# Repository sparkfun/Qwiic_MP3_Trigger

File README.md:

SparkFun Qwiic MP3 Trigger
========================================

[*SparkFun Qwiic MP3 Trigger (DEV-15165)*](https://www.sparkfun.com/products/15165)

This repo is the hardware repo for the Qwiic MP3 Trigger.

Sometimes you just need an MP3 to play. Whether it's a theme song as you enter the room or a pirate cackling when a dollar [gets donated](https://github.com/nseidle/Money_Vacuum) to the kid's museum. The Qwiic MP3 Trigger takes care of all the necessary bits, all you need to do is send a simple I2C command and listen.

The Qwiic MP3 Trigger comes loaded with everything a user may need. Connecting a USB C cable enumerates the Qwiic MP3 Trigger as a jump drive. Simply plug in the Qwiic MP3 Trigger and you'll be transferring MP3s. No need for drivers and no need for WAV or Vorbis conversion! Sound output is provided via a headphone jack or poke-home connector allowing an external speaker to be connected without soldering. The speaker is boosted by a Class-D mono amplifier capable of outputting up to 1.4W. What does 1.4W mean? It's incredibly loud; great for making sure your mech effects are heard on the *con floor and wonderful for annoying your officemates. Volume is software selectable between 32 levels. Equalization can be tuned to be sure your classical hits sound different from your jazz dance routines (in all seriousness EQ selection is available but it's pretty paltry).

And if you don't want to deal with *any* programming, there are four trigger pins. When pin 3 is pulled low the T003.mp3 file will immediately be played. This allows you to start playing sound effects with the touch of a button! By pulling multiple pins down simultaneously the four triggers can play up to ten tracks: T001 to T010.

All settings including volume, EQ, and I2C address are stored in NVM and loaded at each power up. The I2C address of the Qwiic MP3 Trigger can be modified via a solder jumper or be assigned using a software command. Multiple Qwiic MP3 Triggers can be chained together on a single bus allowing for simultaneous track mixing and triggering.

We've written an extensive Arduino library to make MP3 playing over I2C a breeze. Play track X, change volume, play next/previous, check if track is playing, stop play, change EQ, and change I2C address are all supported.

The I2C address of Qwiic MP3 Trigger is software configurable which means you can hookup over 100 on a single I2C bus!

This board is one of our many [Qwiic](https://www.sparkfun.com/qwiic) compatible boards! Simply plug and go. No soldering, no figuring out which is SDA or SCL, and no voltage regulation or translation required!

SparkFun labored with love to create this code. Feel like supporting open source hardware? 
Buy a [breakout board](https://www.sparkfun.com/products/15165) from SparkFun!

Repository Contents
-------------------

* **/Documents** - Datasheets
* **/Hardware** - Eagle design files (.brd, .sch)

Documentation
--------------
* **[Qwiic MP3 Trigger Hookup Guide](https://learn.sparkfun.com/tutorials/qwiic-mp3-trigger-hookup-guide)** - Hookup guide for the Qwiic MP3 Trigger
* **[Installing an Arduino Library Guide](https://learn.sparkfun.com/tutorials/installing-an-arduino-library)** - Basic information on how to install an Arduino library.
* **[Arduino Library](https://github.com/sparkfun/SparkFun_Qwiic_MP3_Trigger_Arduino_Library)** - Library if you decide to use an Arduino via serial I2C.

License Information
-------------------

This product is _**open source**_! 

If you have any questions or concerns on licensing, please contact techsupport@sparkfun.com.

Please use, reuse, and modify these files as you see fit. Please maintain attribution to SparkFun Electronics and release any derivative under the same license.

Distributed as-is; no warranty is given.

- Your friends at SparkFun.

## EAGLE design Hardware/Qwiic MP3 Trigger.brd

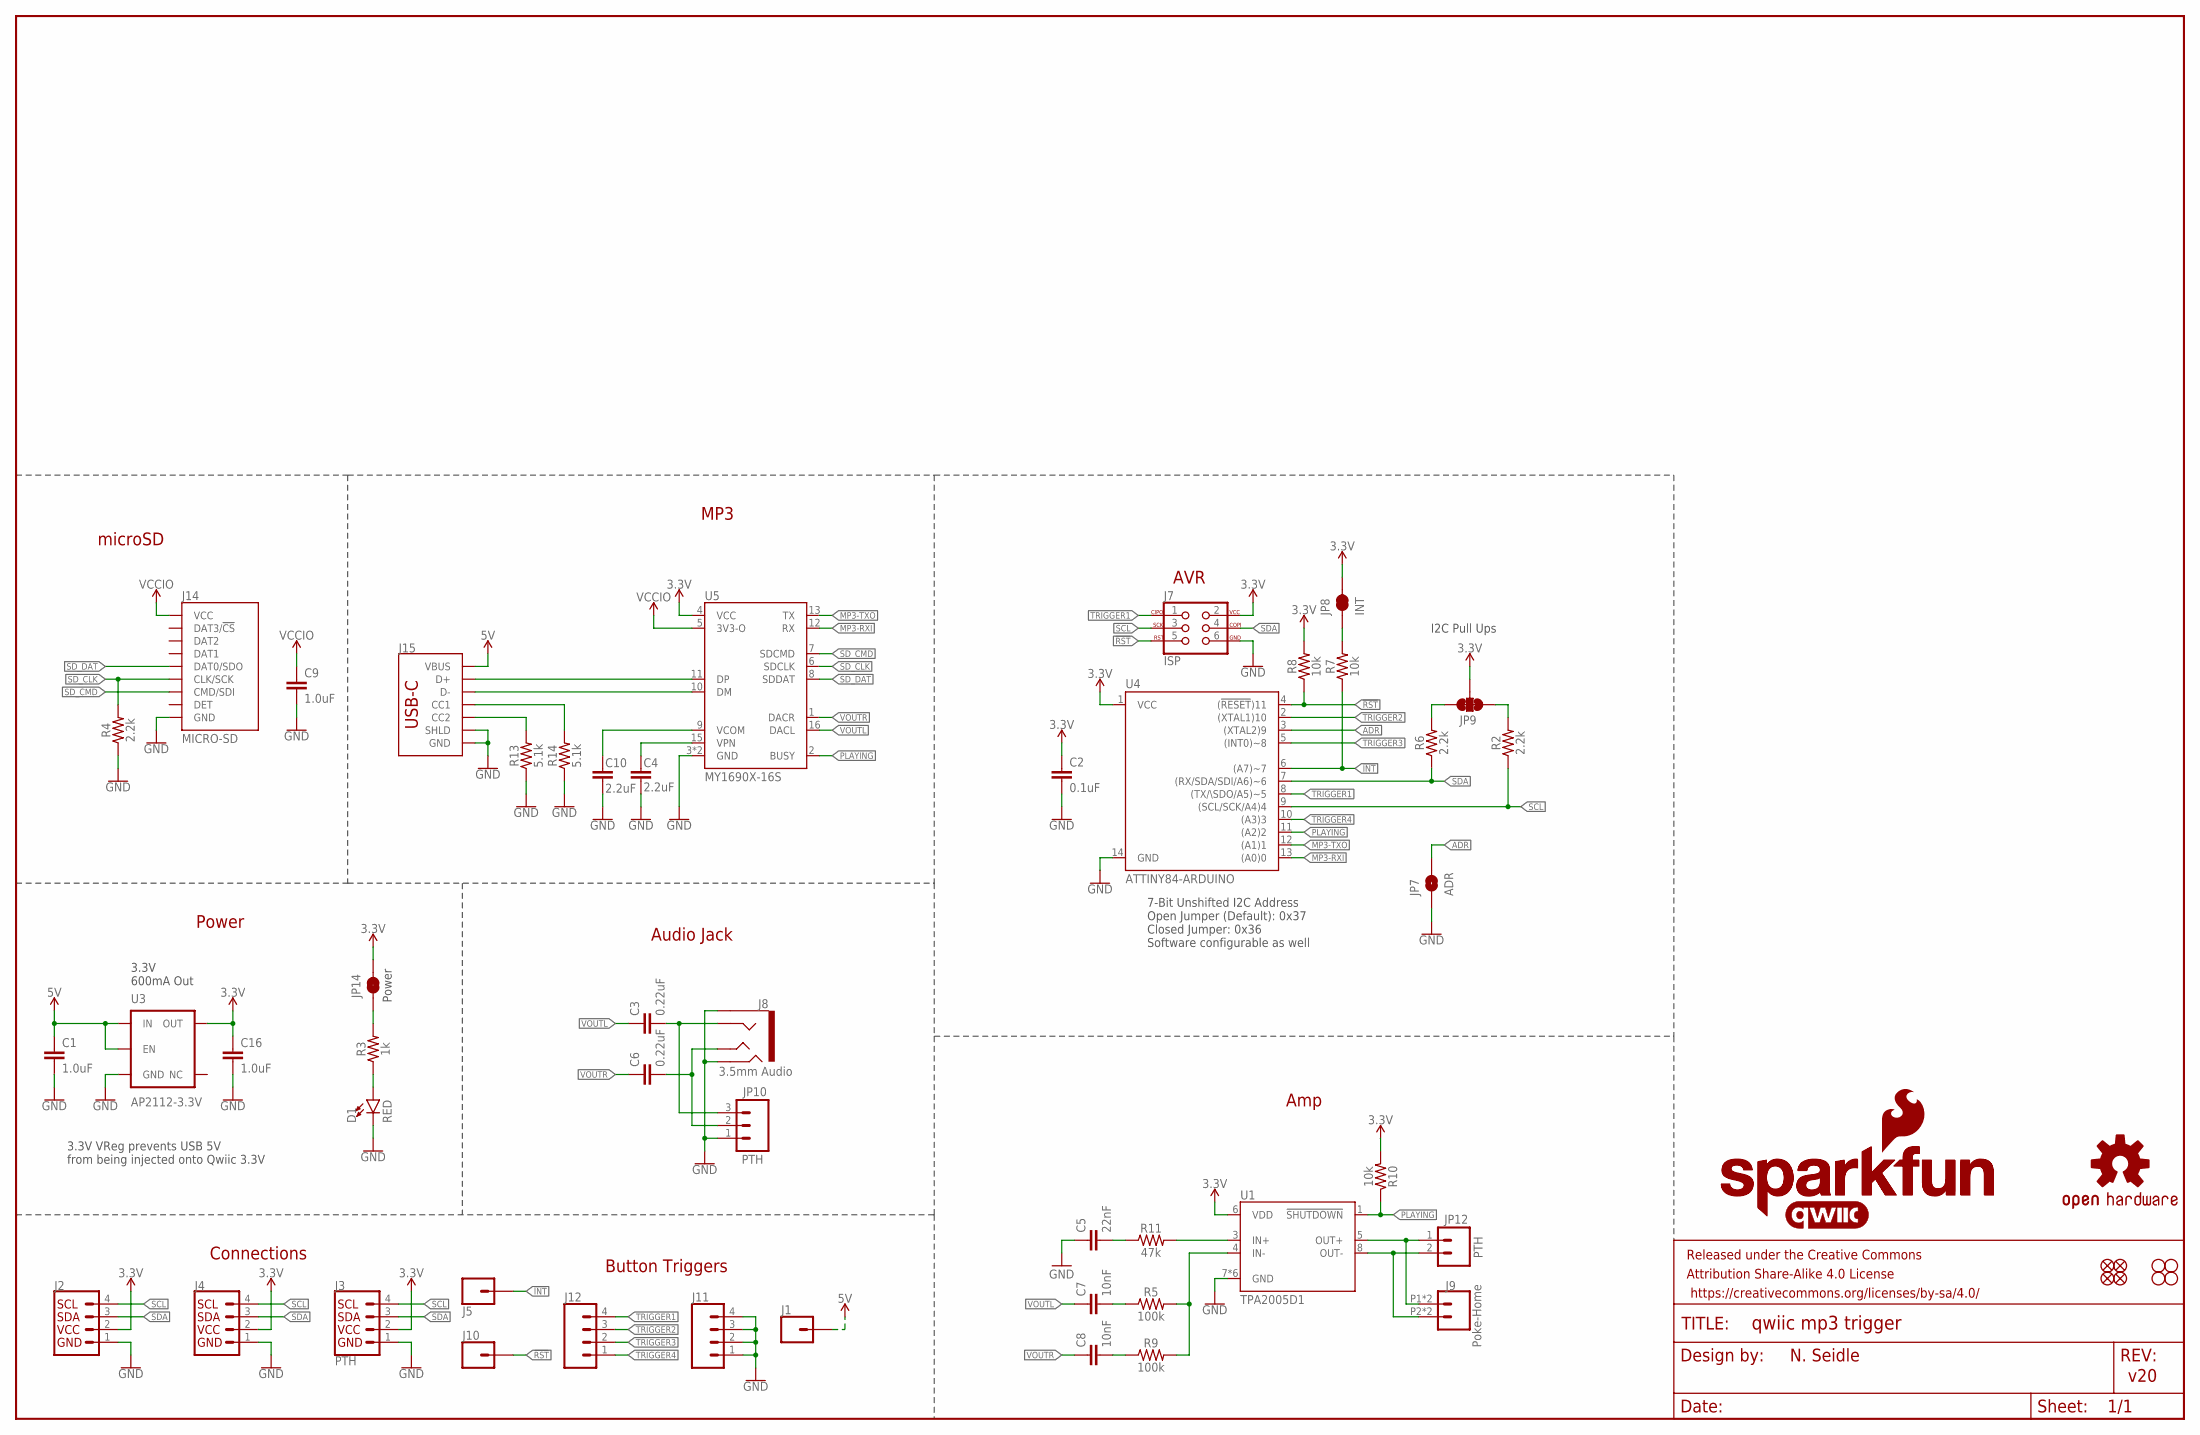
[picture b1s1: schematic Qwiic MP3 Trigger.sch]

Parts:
C1, C9, C16: 1.0uF; 0603
C2: 0.1uF; 0603
C3, C6: 0.22uF; 0603
C4, C10: 2.2uF; 0603
C5: 22nF; 0603
C7, C8: 10nF; 0603
D1: RED; LED-0603
FRAME1: FRAME-LEDGER; CREATIVE_COMMONS
J1, J5, J10: CONN_01PTH_NO_SILK_YES_STOP; 1X01_NO_SILK
J2, J4: QWIIC_RIGHT_ANGLE; JST04_1MM_RA
J3: PTH; 1X04_NO_SILK
J7: ISP; 2X3_TEST_POINTS
J8: 3.5mm Audio; AUDIO_JACK_3.5MM_TRRS_SMD_RA
J9: Poke-Home; 1X02_POKEHOME
J11, J12: CONN_041X04_NO_SILK; 1X04_NO_SILK
J14: MICRO-SD; MICROSD-EXTERNALPIN
J15: USB_C_2-LAYER_PADS; USB-C-16P-2LAYER-PADS
JP1, JP2, JP5, JP6: FIDUCIALUFIDUCIAL; MICRO-FIDUCIAL
JP3, JP4, JP11, JP13: STAND-OFF
JP7: ADR; SMT-JUMPER_2_NO_SILK
JP8: INT; SMT-JUMPER_2_NC_TRACE_SILK
JP9: JUMPER-SMT_3_2-NC_TRACE_SILK; SMT-JUMPER_3_2-NC_TRACE_SILK
JP10: PTH; 1X03_NO_SILK
JP12: PTH; 1X02_NO_SILK
JP14: JUMPER-SMT_2_NC_TRACE_SILK; SMT-JUMPER_2_NC_TRACE_SILK
LOGO1: OSHW-LOGOMINI; OSHW-LOGO-MINI
LOGO2: SFE_LOGO_NAME.1_INCH; SFE_LOGO_NAME_.1
LOGO3: SFE_LOGO_NAME_FLAME.1_INCH; SFE_LOGO_NAME_FLAME_.1
LOGO4: QWIIC_LOGO_CONNECTOR; QWIIC_5.5MM
R2, R4, R6: 2.2k; 0603
R3: 1k; 0603
R5, R9: 100k; 0603
R7, R8, R10: 10k; 0603
R11: 47k; 0603
R13, R14: 5.1k; 0603
U1: TPA2005D1; QFN-8_PAD
U3: AP2112-3.3V; SOT23-5
U4: ATTINY84-ARDUINO; SO14
U5: MY1690X-16S; SO16

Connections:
3.3V: C2.1, C16.1, J2.2, J3.2 (VCC), J4.2, J7.2, JP8.2, JP9.2, JP14.2, R8.2, R10.2, U1.6 (VDD), U3.5 (OUT), U4.1 (VCC), U5.4 (VCC)
5V: C1.1, J1.1, J15.VBUS1 (VBUS), J15.VBUS2 (VBUS), U3.1 (IN), U3.3 (EN)
!INT: J5.1, R7.1, U4.6 ((A7)~7)
!RST: J7.5, J10.1, R8.1, U4.4 ((!RESET!)11)
AC-L: C3.2, J8.RING1, JP10.3
AC-R: C6.2, J8.TIP, JP10.2
ADR: JP7.2, U4.3 ((XTAL2)9)
D+: J15.A6 (D+), J15.B6 (D+), U5.11 (DP)
D-: J15.A7 (D-), J15.B7 (D-), U5.10 (DM)
GND: C1.2, C2.2, C4.2, C5.1, C9.2, C10.2, C16.2, D1.C, J2.1, J3.1 (GND), J4.1, J7.6, J8.EARTH, J8.RING2, J11.1, J11.2, J11.3, J11.4, J14.6 (GND), J14.10 (GND), J14.11 (GND), J14.12 (GND), J14.13 (GND), J15.GND, J15.GND2 (GND), J15.SHLD1 (SHLD), J15.SHLD2 (SHLD), J15.SHLD3 (SHLD), J15.SHLD4 (SHLD), JP7.1, JP10.1, R4.1, R13.1, R14.1, U1.7 (GND), U1.9 (GND), U1.10 (GND), U1.11 (GND), U1.12 (GND), U1.13 (GND), U3.2 (GND), U4.14 (GND), U5.3 (GND), U5.14 (GND)
IN+AMP: R11.2, U1.3 (IN+)
IN-AMP: R5.2, R9.2, U1.4 (IN-)
MP3-RXI: U4.13 ((A0)0), U5.12 (RX)
MP3-TXO: U4.12 ((A1)1), U5.13 (TX)
unnamed: J15.B5 (CC2), R13.2
unnamed: J15.A5 (CC1), R14.2
unnamed: D1.A, R3.1
unnamed: JP8.1, R7.2
unnamed: C8.2, R9.1
unnamed: JP14.1, R3.2
unnamed: C4.1, U5.15 (VPN)
unnamed: C5.2, R11.1
unnamed: C7.2, R5.1
unnamed: C10.1, U5.9 (VCOM)
OUT+: J9.P1 (1), J9.P3 (1), JP12.1, U1.5 (OUT+)
OUT-: J9.P2 (2), J9.P4 (2), JP12.2, U1.8 (OUT-)
PLAYING: R10.1, U1.1 (!SHUTDOWN), U4.11 ((A2)2), U5.2 (BUSY)
SCL: J2.4, J3.4 (SCL), J4.4, J7.3, R2.1, U4.9 ((SCL/SCK/A4)4)
SCL_PU1: JP9.1, R2.2
SDA: J2.3, J3.3 (SDA), J4.3, J7.4, R6.1, U4.7 ((RX/SDA/SDI/A6)~6)
SDA_PU1: JP9.3, R6.2
SD_CLK: J14.5 (CLK/SCK), R4.2, U5.6 (SDCLK)
SD_CMD: J14.3 (CMD/SDI), U5.7 (SDCMD)
SD_DAT: J14.7 (DAT0/SDO), U5.8 (SDDAT)
TRIGGER1: J7.1, J12.4, U4.8 ((TX/\SDO/A5)~5)
TRIGGER2: J12.3, U4.2 ((XTAL1)10)
TRIGGER3: J12.2, U4.5 ((INT0)~8)
TRIGGER4: J12.1, U4.10 ((A3)3)
VCCIO: C9.1, J14.4 (VCC), U5.5 (3V3-O)
VOUTL: C3.1, C7.1, U5.16 (DACL)
VOUTR: C6.1, C8.1, U5.1 (DACR)

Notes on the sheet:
N. Seidle
v20
Power
7-Bit Unshifted I2C Address Open Jumper (Default): 0x37 Closed Jumper: 0x36 Software configurable as well
I2C Pull Ups
3.3V VReg prevents USB 5V from being injected onto Qwiic 3.3V
3.3V 600mA Out
microSD
MP3
AVR
Amp
Connections
Button Triggers
Audio Jack

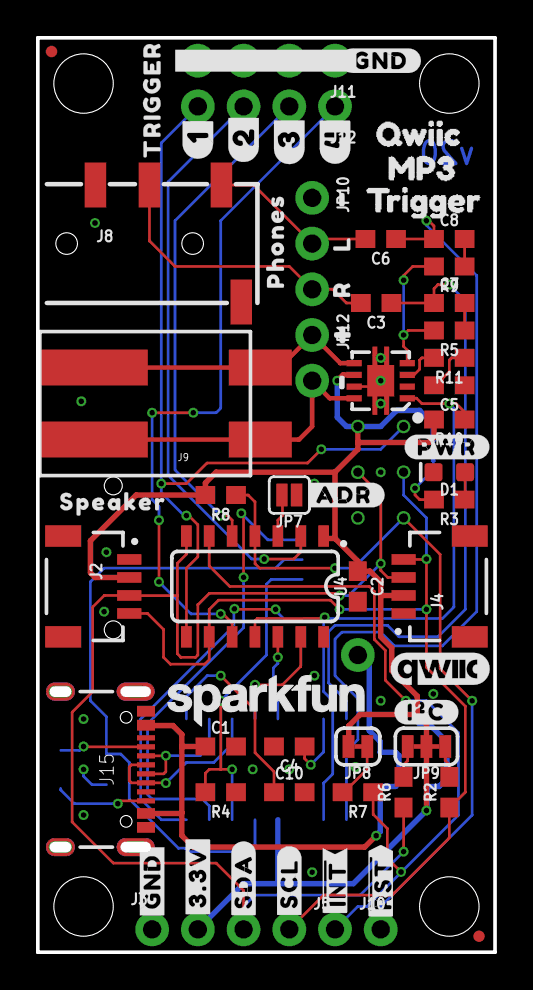
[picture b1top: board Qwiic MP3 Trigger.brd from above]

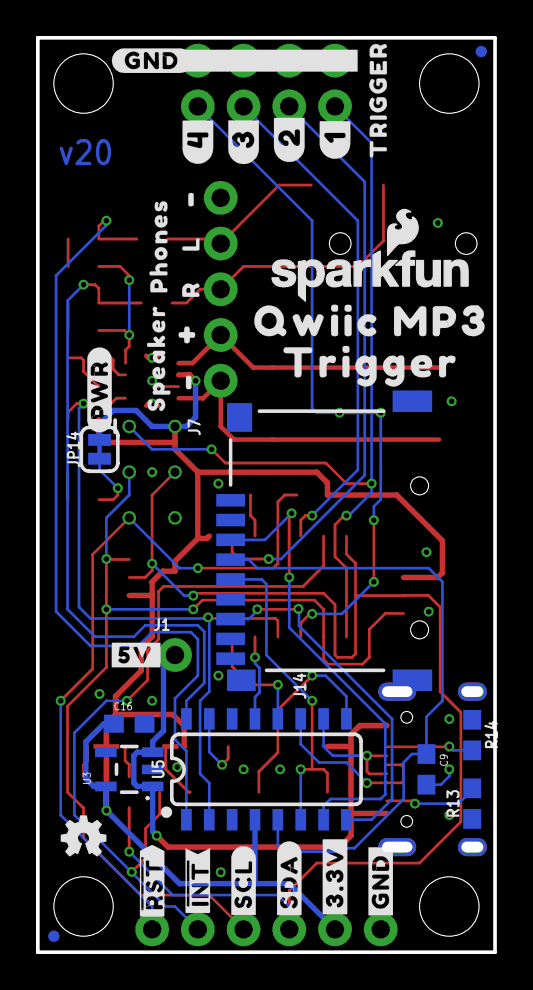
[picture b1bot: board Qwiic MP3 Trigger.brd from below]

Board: 2 copper layers, 25.4 x 50.8 mm, 108 parts (38 on the bottom side), 41 nets.

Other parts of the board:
U$1: MP31
U$2, U$47: TRIGGER0
U$3: #5V#0
U$10, U$38: #1#3
U$12, U$28: #1
U$14, U$51: #0
U$15, U$24: #PWR#0
U$17: #ADR#0
U$18, U$40: SPEAKER0
U$19, U$31: #GND#0
U$20: #I�C#0
U$23: QWIIC0
U$25: QWIIC_MP30
U$29, U$45: L1
U$32, U$48: PHONES0
U$33, U$34: ##INT##4
U$35, U$36: ##RST##5
U$37, U$39: R0
U$41, U$43: #2
U$42, U$44: #3#3V#0
U$46, U$58: #GND#1
U$49, U$53: #2#2
U$50: TRIGGER2
U$52: TRIGGER1
U$54, U$55: #3#1
U$56, U$57: #4#0
U$59, U$60: #SCL#3
U$61, U$62: #SDA#2

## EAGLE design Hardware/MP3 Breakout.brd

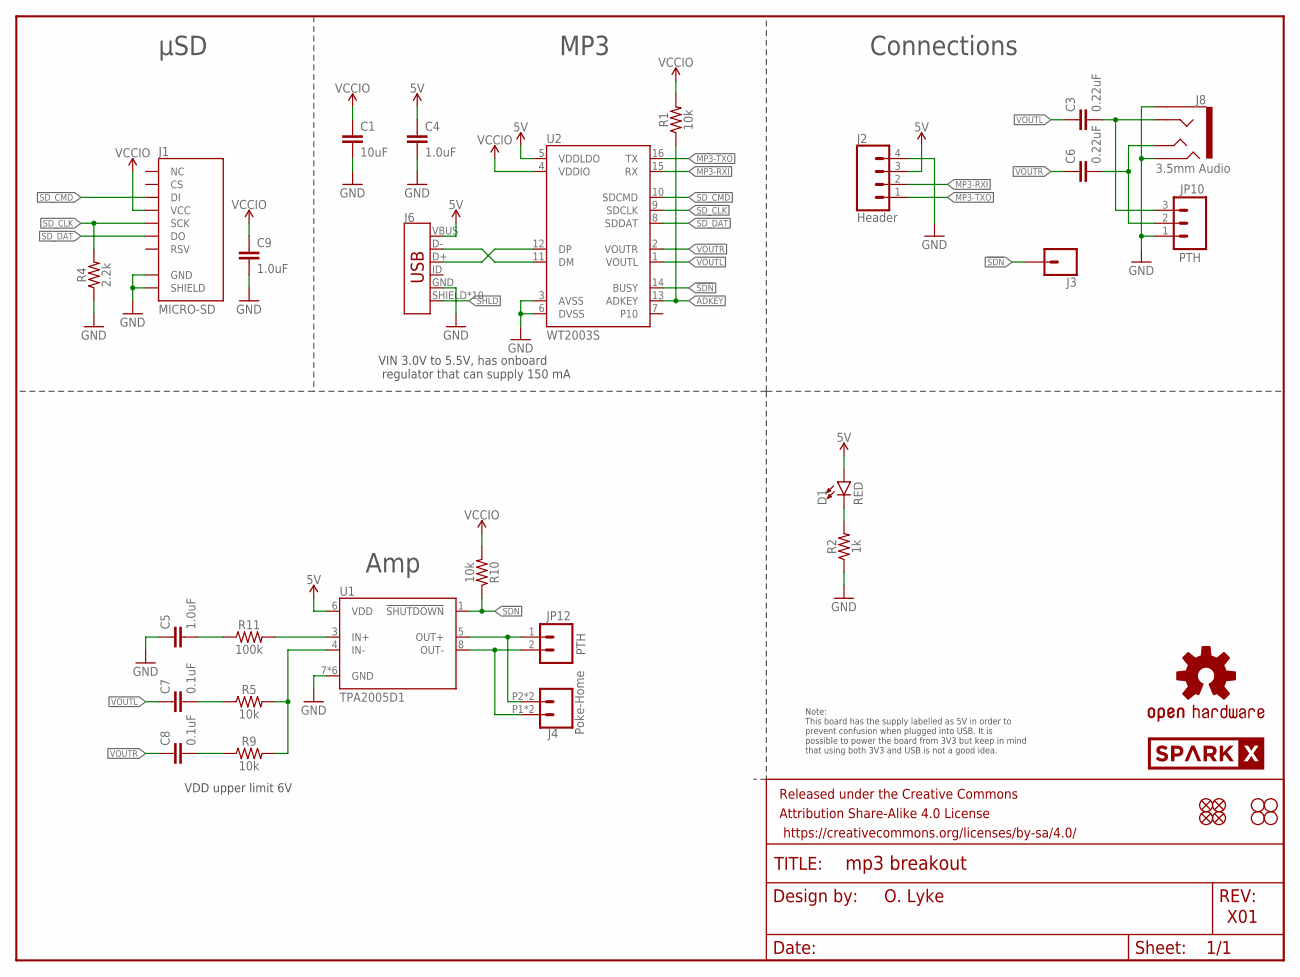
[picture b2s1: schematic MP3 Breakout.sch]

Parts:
C1: 10uF; 0603
C3, C6: 0.22uF; 0603
C4, C5, C9: 1.0uF; 0603
C7, C8: 0.1uF; 0603
D1: RED; LED-0603
FRAME1: FRAME-LETTER; CREATIVE_COMMONS
J1: MICRO-SD; MICRO-SD-SOCKET
J2: Header; 1X04_NO_SILK
J3: CONN_01PTH_NO_SILK_YES_STOP; 1X01_NO_SILK
J4: Poke-Home; 1X02_POKEHOME
J6: USB_MICRO-B_HALF_PTH_MILL; USB-MICROB-PTH-MILL
J8: 3.5mm Audio; AUDIO_JACK_3.5MM_TRRS_SMD_RA
JP1, JP2, JP5, JP6: FIDUCIALUFIDUCIAL; MICRO-FIDUCIAL
JP3, JP4, JP11, JP13: STAND-OFF
JP10: PTH; 1X03_NO_SILK
JP12: PTH; 1X02_NO_SILK
LOGO1: OSHW-LOGOMINI; OSHW-LOGO-MINI
R1, R5, R9, R10: 10k; 0603
R2: 1k; 0603
R4: 2.2k; 0603
R11: 100k; 0603
U1: TPA2005D1; QFN-8_PAD
U2: WT2003S; SO16
U$2: SPARKX-LOGO4; SPARKX-MEDIUM

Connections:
5V: C4.1, D1.A, J2.3, J6.VBUS, U1.6 (VDD), U2.5 (VDDLDO)
!SDN: J3.1, R10.1, U1.1 (!SHUTDOWN), U2.14 (BUSY)
AC-L: C3.2, J8.RING1, JP10.3
AC-R: C6.2, J8.TIP, JP10.2
ADKEY: R1.1, U2.13 (ADKEY)
D+: J6.D+, U2.12 (DP)
D-: J6.D-, U2.11 (DM)
GND: C1.2, C4.2, C5.1, C9.2, J1.CD1 (SHIELD), J1.GND, J2.4, J6.GND, J8.EARTH, J8.RING2, JP10.1, R2.1, R4.1, U1.7 (GND), U1.9 (GND), U1.10 (GND), U1.11 (GND), U1.12 (GND), U1.13 (GND), U2.3 (AVSS), U2.6 (DVSS)
IN+AMP: R11.2, U1.3 (IN+)
IN-AMP: R5.2, R9.2, U1.4 (IN-)
MP3-RXI: J2.2, U2.15 (RX)
MP3-TXO: J2.1, U2.16 (TX)
unnamed: D1.C, R2.2
unnamed: C8.2, R9.1
unnamed: C5.2, R11.1
unnamed: C7.2, R5.1
OUT+: J4.P2 (2), J4.P4 (2), JP12.1, U1.5 (OUT+)
OUT-: J4.P1 (1), J4.P3 (1), JP12.2, U1.8 (OUT-)
SD_CLK: J1.SCLK (SCK), R4.2, U2.9 (SDCLK)
SD_CMD: J1.DI, U2.10 (SDCMD)
SD_DAT: J1.DO, U2.8 (SDDAT)
SHLD: J6.SHIELD, J6.SHIELD2 (SHIELD), J6.SHIELD3 (SHIELD), J6.SHIELD4 (SHIELD), J6.SHIELD5 (SHIELD), J6.SHIELD6 (SHIELD), J6.SHIELD7 (SHIELD), J6.SHIELD8 (SHIELD), J6.SHIELD9 (SHIELD), J6.SHIELD10 (SHIELD)
VCCIO: C1.1, C9.1, J1.VCC, R1.2, R10.2, U2.4 (VDDIO)
VOUTL: C3.1, C7.1, U2.1 (VOUTL)
VOUTR: C6.1, C8.1, U2.2 (VOUTR)

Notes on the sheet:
O. Lyke
X01
μSD
MP3
Amp
Connections
VIN 3.0V to 5.5V, has onboard regulator that can supply 150 mA
VDD upper limit 6V
Note: This board has the supply labelled as 5V in order to prevent confusion when plugged into USB. It is possible to power the board from 3V3 but keep in mind that using both 3V3 and USB is not a good idea.

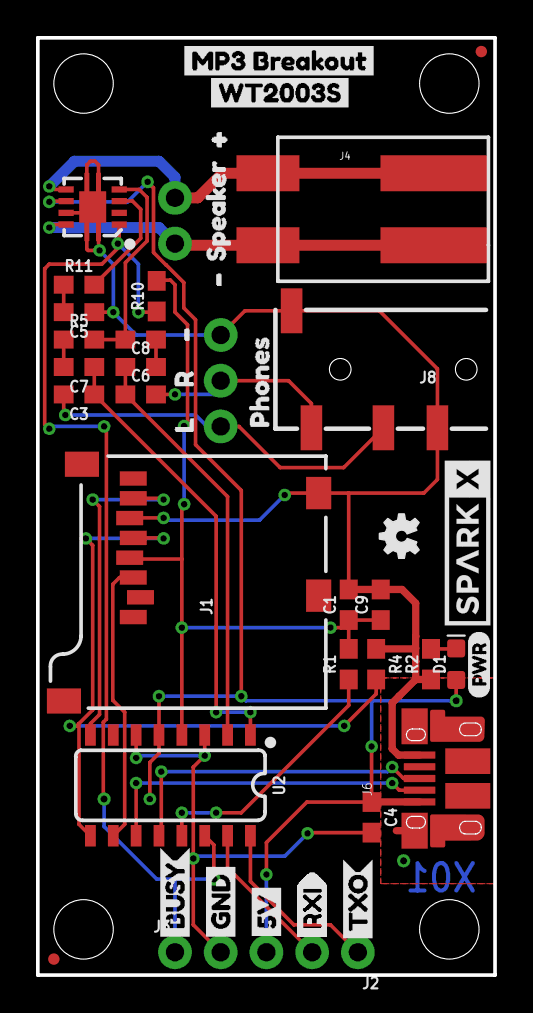
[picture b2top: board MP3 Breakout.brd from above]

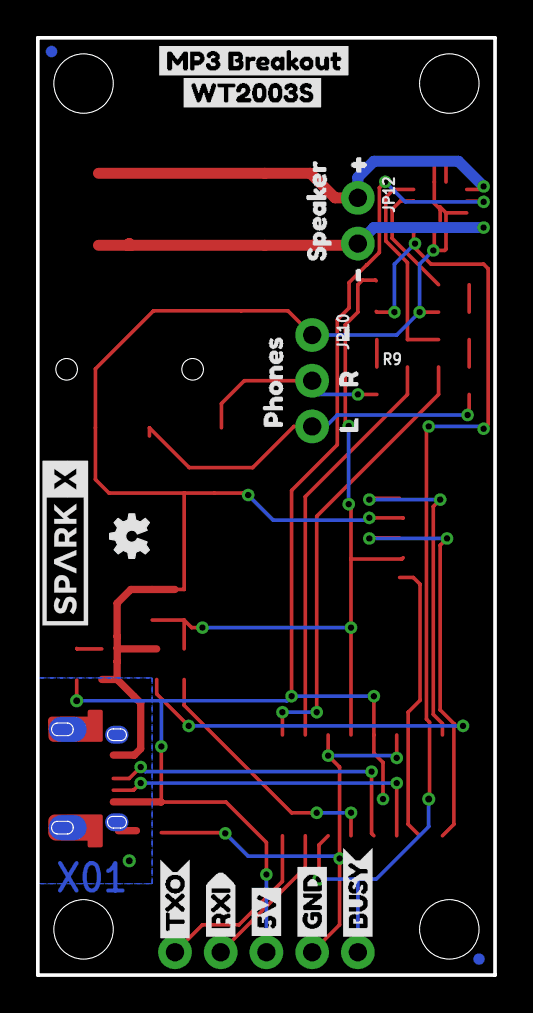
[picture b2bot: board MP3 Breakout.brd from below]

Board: 2 copper layers, 25.4 x 52.1 mm, 69 parts (20 on the bottom side), 25 nets.

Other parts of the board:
LOGO2: OSHW-LOGOMINI; OSHW-LOGO-MINI@1
U$1, U$22: GND1
U$3, U$41: L12
U$4, U$39: R11
U$6, U$9: TXO0
U$7, U$8, U$23: RXI0
U$10, U$15, U$21, U$25: #6
U$11: SPARKX-LOGO4; SPARKX-MEDIUM
U$12, U$24: MP3_BREAKOUT0
U$13, U$14: BUSY0
U$16, U$40: PHONES0
U$17: PWR-()-03
U$18, U$20: SPEAKER1
U$19, U$28: #5
U$26, U$27: WT2003S0
U$29, U$30: 5V0

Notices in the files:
Firmware/Qwiic_MP3_Controller/Qwiic_MP3_Controller.ino:
License: This code is public domain but you buy me a beer if you use this and we meet someday (Beerware license).
parts and their libraries:
SparkFun-Connectors: Licensing: Creative Commons ShareAlike 4.0 International - https://creativecommons.org/licenses/by-sa/4.0
SparkFun-Aesthetics: Released under the Creative Commons Attribution Share-Alike 4.0 License
SparkFun-Aesthetics: https://creativecommons.org/licenses/by-sa/4.0
